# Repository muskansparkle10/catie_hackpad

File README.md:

# Catie Hackpad

Catie Hackpad is a 4 keys macropad with 4 Leds and uses KMK Firmware.

## Features 

- Dual layer case
- 4 RGB LEDs
- 4 Keys

## Schematic

## PCB

## CAD Model

## BOM

- 4x Cherry MX Switches
- 4x DSA Keycaps
- 4x M3x16mm SHCS Bolts
- 4x SK6812 MINI-E LEDs
- 1x XIAO RP2040
- 1x Case (2 printed parts)
- 1x PCB

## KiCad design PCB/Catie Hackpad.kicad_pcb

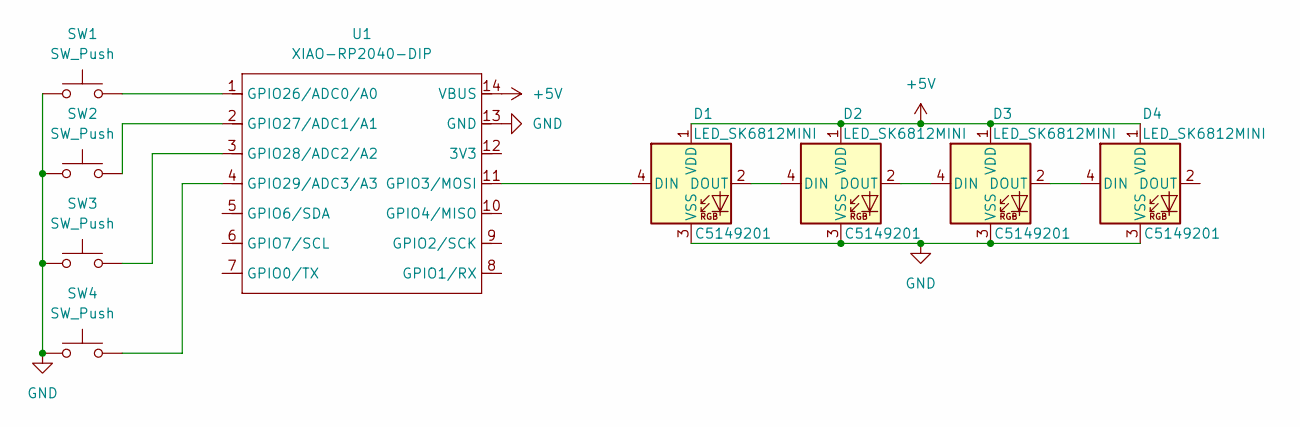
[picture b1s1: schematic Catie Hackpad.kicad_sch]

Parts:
D1, D2, D3, D4: LED_SK6812MINI; MX_SK6812MINI-E_REV; LCSC C5149201
SW1, SW2, SW3, SW4: SW_Push; SW_Cherry_MX_1.00u_PCB
U1: XIAO-RP2040-DIP

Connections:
+5V: D1.1 (VDD), D2.1 (VDD), D3.1 (VDD), D4.1 (VDD), U1.14 (VBUS)
GND: D1.3 (VSS), D2.3 (VSS), D3.3 (VSS), D4.3 (VSS), SW1.1, SW2.1, SW3.1, SW4.1, U1.13 (GND)
unnamed: D1.4 (DIN), U1.11 (GPIO3/MOSI)
unnamed: D1.2 (DOUT), D2.4 (DIN)
unnamed: D2.2 (DOUT), D3.4 (DIN)
unnamed: D3.2 (DOUT), D4.4 (DIN)
unnamed: SW1.2, U1.1 (GPIO26/ADC0/A0)
unnamed: SW2.2, U1.2 (GPIO27/ADC1/A1)
unnamed: SW3.2, U1.3 (GPIO28/ADC2/A2)
unnamed: SW4.2, U1.4 (GPIO29/ADC3/A3)

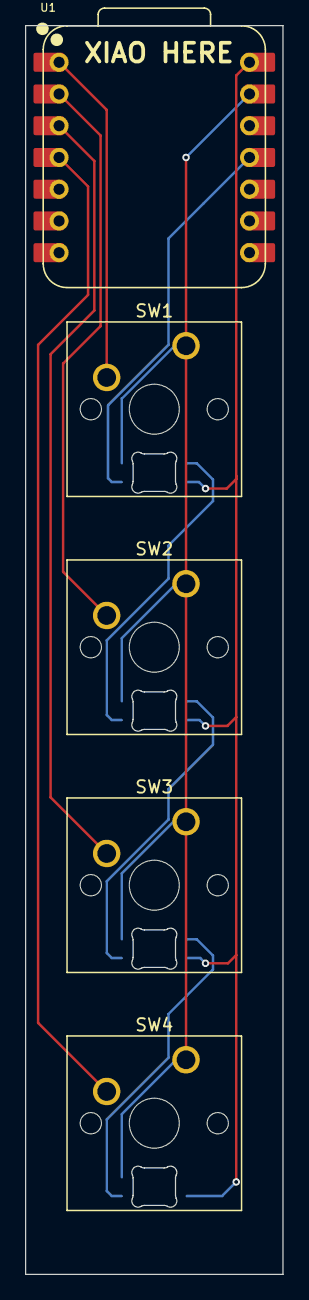
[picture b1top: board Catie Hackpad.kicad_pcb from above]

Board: 2 copper layers, 20.6 x 100.0 mm, 9 parts (0 on the bottom side), 10 nets.

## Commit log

2026-03-07 Add README
